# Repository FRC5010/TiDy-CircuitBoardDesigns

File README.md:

# 1. TiDy - Circuit Board Designs

FRC 5010 - Tiger Dynasty circuit board designs repository.

- [1. TiDy - Circuit Board Designs](#1-tidy---circuit-board-designs)
  - [1.1. CanTerm 1.0](#11-canterm-10)
  - [1.2. Libraries](#12-libraries)

## 1.1. CanTerm 1.0

Current Version: 1.0

CAN Termination project to terminate the CAN bus on a robot with a Molex SL Male connector and mounting hole

## 1.2. Libraries

FRC 5010 Footprint Library with parts not in the custom library

- Molex SL Right Angle Through Hole 1x02

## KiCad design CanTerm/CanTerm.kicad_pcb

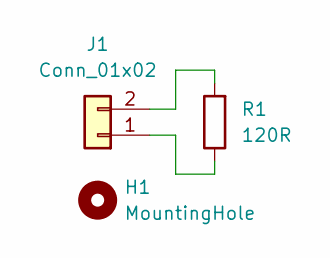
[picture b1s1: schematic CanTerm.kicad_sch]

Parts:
H1: MountingHole; MountingHole_5mm
J1: Conn_01x02; Molex_SL_RightAngle_Through_1x02
R1: 120R; R_1206_3216Metric_Pad1.30x1.75mm_HandSolder

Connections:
unnamed: J1.1, R1.1
unnamed: J1.2, R1.2

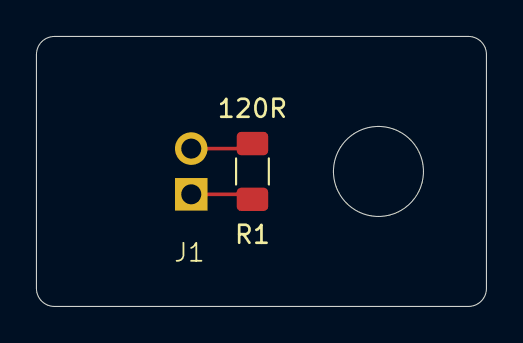
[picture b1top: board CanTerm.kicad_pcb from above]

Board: 2 copper layers, 25.0 x 15.0 mm, 3 parts (0 on the bottom side), 2 nets.

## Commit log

2024-04-30 Added CanTerm Project
2024-04-30 Added basic VS Code extensions Updated README
2024-05-01 Added molexSL footprint and improved CanTerm
2024-05-01 Standards update
2024-05-01 README update
